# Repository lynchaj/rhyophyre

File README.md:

# rhyophyre
Single Board Computer featuring Zilog Z180 processor and NEC µPD7220 Graphics Display Controller

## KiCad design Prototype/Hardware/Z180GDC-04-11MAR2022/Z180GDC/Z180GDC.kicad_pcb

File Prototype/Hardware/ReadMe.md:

# rhyophyre prototype hardware folder

Contains KiCAD EDA files for schematic, PCB layout, 3D render, Bill of Materials, etc.

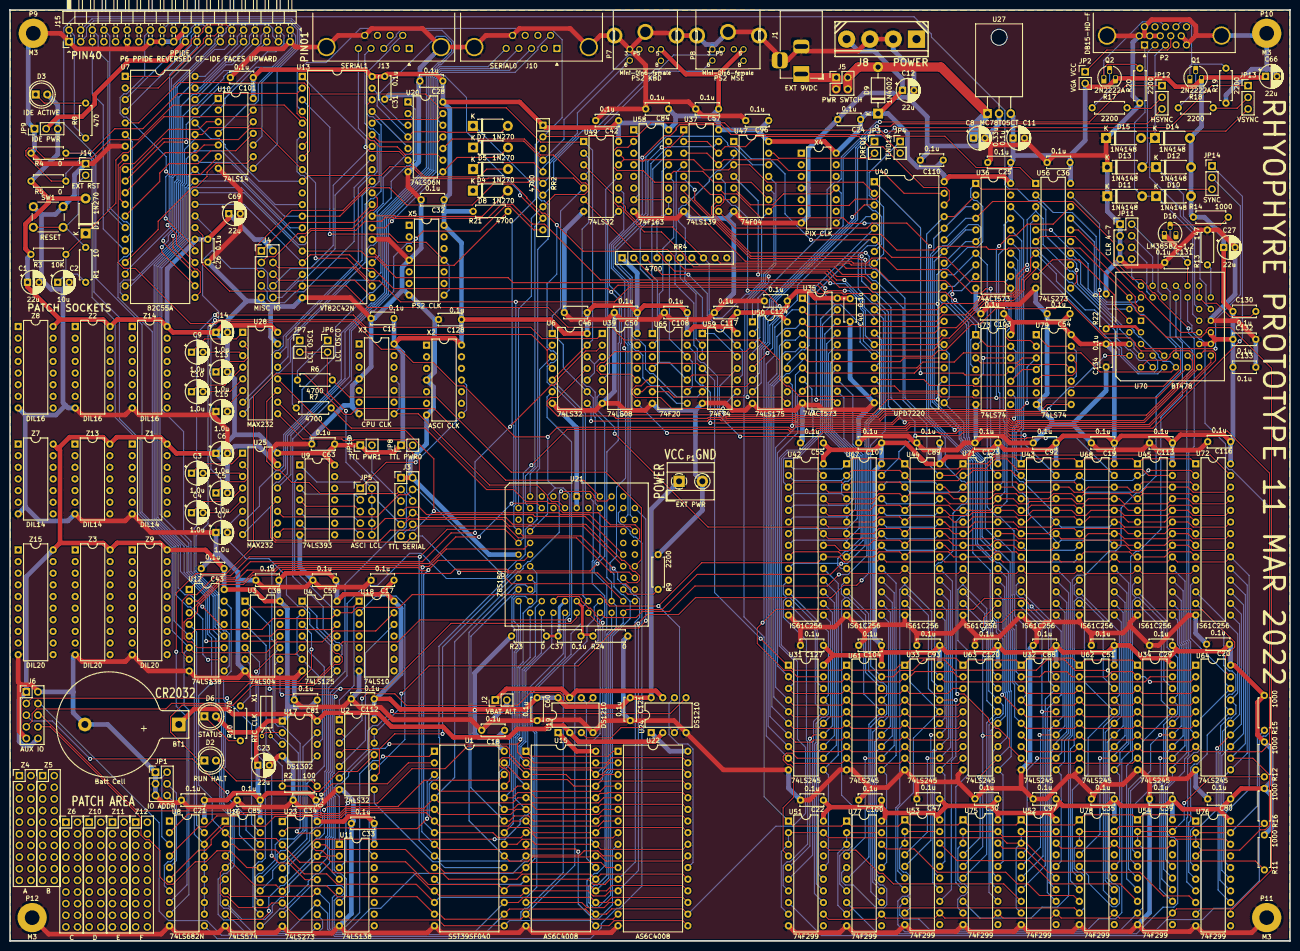
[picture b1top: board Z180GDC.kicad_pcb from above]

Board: 2 copper layers, 279.4 x 203.2 mm, 249 parts (0 on the bottom side), 388 nets.

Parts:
BT1: Batt Cell; BatteryHolder_Keystone_103_1x20mm
C1, C12, C23, C27, C66, C69: 22u; CP_Radial_D5.0mm_P2.50mm
C2: 10u; CP_Radial_D5.0mm_P2.50mm
C3, C4, C5, C6, C7, C9, C10, C13, C14, C15: 1.0u; CP_Radial_D5.0mm_P2.50mm
C8: 0.33u; CP_Radial_D5.0mm_P2.50mm
C11: 0.1u; CP_Radial_D5.0mm_P2.50mm
C16, C17, C18, C19, C20, C21, C22, C24, C25, C26, C28, C29, C30, C31, C32, C33, C34, C35, C36, C37, C38, C39, C40, C42, C43, C46, C47, C50, C51, C54, C55, C57, C59, C60, C63, C80, C81, C84, C85, C88, C89, C92, C93, C96, C97, C100, C101, C103, C104, C107, C108, C110, C112, C113, C116, C117, C120, C121, C123, C124, C127, C128, C130, C131, C132, C133, C134: 0.1u; C_Disc_D5.0mm_W2.5mm_P5.00mm
D1, D4, D5, D7, D8: 1N270; D_DO-41_SOD81_P7.62mm_Horizontal
D2: RUN HALT; LED_D5.0mm
D3: IDE ACTIVE; LED_D5.0mm
D6: STATUS; LED_D5.0mm
D9: 1N4002; D_DO-41_SOD81_P10.16mm_Horizontal
D10, D11, D12, D13, D14, D15: 1N4148; D_DO-41_SOD81_P7.62mm_Horizontal
D16: LM385BZ-1.2; TO-92L_HandSolder
J1: EXT 9VDC; BarrelJack_Horizontal
J2: VBAT ALT; PinHeader_1x02_P2.54mm_Vertical
J3: TTL SERIAL; PinHeader_2x06_P2.54mm_Vertical
J4: MISC IO; PinHeader_2x05_P2.54mm_Vertical
J5: PWR SWTCH; PinHeader_2x02_P2.54mm_Vertical
J6: AUX IO; PinHeader_2x05_P2.54mm_Vertical
J8: POWER; molex-drive-connector
J10: SERIAL0; DSUB-9_Male_Horizontal_P2.77x2.84mm_EdgePinOffset4.94mm_Hou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
J13: SERIAL1; DSUB-9_Male_Horizontal_P2.77x2.84mm_EdgePinOffset4.94mm_Hou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
J14: EXT RST; PinHeader_1x02_P2.54mm_Vertical
J15: PPIDE; PinHeader_2x20_P2.54mm_Horizontal
JP1: IO ADDR; PinHeader_2x03_P2.54mm_Vertical
JP2: VGA VCC; PinHeader_1x02_P2.54mm_Vertical
JP3: DREQ1; PinHeader_1x02_P2.54mm_Vertical
JP4: TEND1#; PinHeader_1x02_P2.54mm_Vertical
JP5: ASCI LCL; PinHeader_2x05_P2.54mm_Vertical
JP6: LCL OSC0; PinHeader_1x02_P2.54mm_Vertical
JP7: LCL OSC1; PinHeader_1x02_P2.54mm_Vertical
JP8: TTL PWR0; PinHeader_1x02_P2.54mm_Vertical
JP9: IDE PWR; PinHeader_1x03_P2.54mm_Vertical
JP10: TTL PWR1; PinHeader_1x02_P2.54mm_Vertical
JP11: CLR 4-7; PinHeader_2x04_P2.54mm_Vertical
JP12: HSYNC; PinHeader_1x03_P2.54mm_Vertical
JP13: VSYNC; PinHeader_1x03_P2.54mm_Vertical
JP14: SYNC; PinHeader_1x03_P2.54mm_Vertical
P1: EXT PWR; TerminalBlock_MetzConnect_Type101_RT01602HBWC_1x02_P5.08mm_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
P2: DB15-HD-F; DSUB-15-HD_Female_Horizontal_P2.29x1.98mm_EdgePinOffset3.03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
P7: PS2 KBD; mini-din6-female
P8: PS2 MSE; mini-din6-female
P9, P10, P11, P12: M3; MountingHole_3.2mm_M3_Pad
Q1, Q2: 2N2222A; TO-92L_HandSolder
R1: 10; R_Axial_DIN0207_L6.3mm_D2.5mm_P7.62mm_Horizontal
R2: 100; R_Axial_DIN0207_L6.3mm_D2.5mm_P7.62mm_Horizontal
R3: 10K; R_Axial_DIN0207_L6.3mm_D2.5mm_P7.62mm_Horizontal
R4, R5, R22, R23, R24: 0; R_Axial_DIN0207_L6.3mm_D2.5mm_P7.62mm_Horizontal
R6, R7, R21: 4700; R_Axial_DIN0207_L6.3mm_D2.5mm_P7.62mm_Horizontal
R8, R10: 470; R_Axial_DIN0207_L6.3mm_D2.5mm_P7.62mm_Horizontal
R9, R17, R18, R19, R20: 2200; R_Axial_DIN0207_L6.3mm_D2.5mm_P7.62mm_Horizontal
R11, R12, R14, R15, R16: 1000; R_Axial_DIN0207_L6.3mm_D2.5mm_P7.62mm_Horizontal
R13: 147; R_Axial_DIN0207_L6.3mm_D2.5mm_P7.62mm_Horizontal
RR2, RR4: 4700; R_Array_SIP10
SW1: RESET; SW_PUSH_6mm
U1: SST39SF040; DIP-32_W15.24mm
U2, U6, U49: 74LS32; DIP-14_W7.62mm
U3: 74LS04; DIP-14_W7.62mm
U4: 74LS125; DIP-14_W7.62mm
U7: 82C55A; DIP-40_W15.24mm
U8: 74LS682N; DIP-20_W7.62mm
U9: 74LS393; DIP-14_W7.62mm
U10: 74LS14; DIP-14_W7.62mm
U11, U12: 74LS138; DIP-16_W7.62mm
U13: VT82C42N; DIP-40_W15.24mm
U15, U22: AS6C4008; DIP-32_W15.24mm
U16: 74LS574; DIP-20_W7.62mm
U17: DS1302; DIP-8_W7.62mm
U18: 74LS10; DIP-14_W7.62mm
U19, U24: DS1210; DIP-8_W7.62mm
U20: 74LS06N; DIP-14_W7.62mm
U21: Z8S180; PLCC-68_THT-Socket
U23, U56: 74LS273; DIP-20_W7.62mm
U25, U28: MAX232; DIP-16_W7.62mm
U27: MC78T05CT; TO-220-3_Horizontal_TabDown
U31, U32, U33, U34, U61, U62, U63, U64: 74LS245; DIP-20_W7.62mm
U35, U36: 74ACT573; DIP-20_W7.62mm
U37: 74LS139; DIP-16_W7.62mm
U39: 74LS08; DIP-14_W7.62mm
U40: UPD7220; DIP-40_W15.24mm
U42, U43, U44, U45, U67, U68, U71, U72: IS61C256; DIP-28_W7.62mm
U47: 74F04; DIP-14_W7.62mm
U50: 74LS175; DIP-16_W7.62mm
U51, U52, U53, U54, U75, U76, U77, U78: 74F299; DIP-20_W7.62mm
U58: 74F163; DIP-16_W7.62mm
U59: 74F74; DIP-14_W7.62mm
U65: 74F20; DIP-14_W7.62mm
U70: BT478; PLCC-44_THT-Socket
U73, U79: 74LS74; DIP-14_W7.62mm
X1: RTC CLK; Crystal_C26-LF_D2.1mm_L6.5mm_Horizontal
X2: ASCI CLK; DIP-14_W7.62mm
X3: CPU CLK; DIP-14_W7.62mm
X4: PIX CLK; DIP-14_W7.62mm
X5: PS2 CLK; DIP-14_W7.62mm
Z1, Z7, Z13: DIL14; DIP-14_W7.62mm
Z2, Z8, Z14: DIL16; DIP-16_W7.62mm
Z3, Z9, Z15: DIL20; DIP-20_W7.62mm
Z4: A; PinHeader_2x10_P2.54mm_Vertical
Z5: B; PinHeader_2x10_P2.54mm_Vertical
Z6: C; PinHeader_2x10_P2.54mm_Vertical
Z10: D; PinHeader_2x10_P2.54mm_Vertical
Z11: E; PinHeader_2x10_P2.54mm_Vertical
Z12: F; PinHeader_2x10_P2.54mm_Vertical

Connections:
/2xWCLK: RR4.8, U40.1, U47.8, U49.9, U73.11, U79.11
/2xWCLK#: U47.9, U58.12, U59.11, U65.4, U65.10, U73.3, U79.3
/8-16: U56.19, U70.2
/9VDC: J1.1, J5.1, J5.3
/A0: U1.12, U7.9, U13.9, U15.12, U21.14, U22.12, U40.11, U70.17
/A1: U1.11, U7.8, U15.11, U21.15, U22.11, U70.18
/A2: U1.10, U12.1, U15.10, U21.16, U22.10, U70.19
/A3: U1.9, U12.2, U15.9, U21.17, U22.9
/A4: U1.8, U12.3, U15.8, U21.19, U22.8
/A5: U1.7, U8.6, U15.7, U21.20, U22.7
/A6: U1.6, U8.4, U15.6, U21.21, U22.6
/A7: U1.5, U8.2, U15.5, U21.22, U22.5
/A8: U1.27, U15.27, U21.23, U22.27
/A9: U1.26, U15.26, U21.24, U22.26
/A10: U1.23, U15.23, U21.25, U22.23
/A11: U1.25, U15.25, U21.26, U22.25
/A12: U1.4, U15.4, U21.27, U22.4
/A13: U1.28, U15.28, U21.28, U22.28
/A14: U1.29, U15.3, U21.29, U22.3
/A15: U11.1, U15.31, U21.30, U22.31
/A15_ROM: U1.3, U23.2
/A16: U11.2, U15.2, U21.31, U22.2
/A16_ROM: U1.2, U23.5
/A17: U11.3, U15.30, U21.32, U22.30
/A17_ROM: U1.30, U23.6
/A18: U11.5, U15.1, U21.33, U22.1
/A18_ROM: U1.1, U23.9
/A19: U3.1, U11.4, U21.35
/A19_ROM: J6.4, U23.12
/AD0: U31.2, U33.2, U35.9, U40.22, U61.2, U63.2
/AD1: U31.3, U33.3, U35.8, U40.23, U61.3, U63.3
/AD2: U31.4, U33.4, U35.7, U40.24, U61.4, U63.4
/AD3: U31.5, U33.5, U35.6, U40.25, U61.5, U63.5
/AD4: U31.6, U33.6, U35.5, U40.26, U61.6, U63.6
/AD5: U31.7, U33.7, U35.4, U40.27, U61.7, U63.7
/AD6: U31.8, U33.8, U35.3, U40.28, U61.8, U63.8
/AD7: U31.9, U33.9, U35.2, U40.29, U61.9, U63.9
/AD8: U32.2, U34.2, U36.9, U40.30, U62.2, U64.2
/AD9: U32.3, U34.3, U36.8, U40.31, U62.3, U64.3
/AD10: U32.4, U34.4, U36.7, U40.32, U62.4, U64.4
/AD11: U32.5, U34.5, U36.6, U40.33, U62.5, U64.5
/AD12: U32.6, U34.6, U36.5, U40.34, U62.6, U64.6
/AD13: U32.7, U34.7, U36.4, U40.35, U62.7, U64.7
/AD14: U32.8, U34.8, U36.3, U40.36, U62.8, U64.8
/AD15: U32.9, U34.9, U36.2, U40.37, U62.9, U64.9
/AD16: U37.2, U37.14, U40.38
/AD17: U37.3, U37.13, U40.39
/ALE: U35.11, U36.11, U40.6, U47.1, U79.2
/ALE2#: U49.10, U79.8
/ALE#: U47.2, U59.1, U59.12
/BLANK#: U50.11, U70.7
/BLU: D14.1, D15.2, P2.3, U70.27
/BUF_Q0: J6.3, U16.19
/BUF_Q1: J6.5, U16.18
/BUF_Q2: J6.6, U16.17
/BUF_Q3: J6.8, U16.16
/BUF_Q4: U16.15, U17.5
/BUF_Q5: U4.4, U16.14
/BUF_Q6: U16.13, U17.7
/BUF_Q7: U4.5, U16.12
/COLOR0: U51.8, U70.32
/COLOR1: U70.33, U77.8
/COLOR2: U53.8, U70.34
/COLOR3: U70.35, U75.8
/COLOR4: JP11.2, U70.36
/COLOR5: JP11.4, U70.37
/COLOR6: JP11.6, U70.38
/COLOR7: JP11.8, U70.39
/CS_ACR#: U12.15, U23.11
/CS_GDC#: U12.11, U49.2, U49.4
/CS_KM#: U12.12, U13.6
/CS_LATCH#: U12.10, U56.11
/CS_PPI#: U7.6, U12.13
/CS_RAMDAC0#: U12.9, U39.1
/CS_RAMDAC1#: U12.7, U39.2
/CS_RAMDAC#: U6.10, U6.12, U39.3
/CS_RAMHI#: U2.3, U19.5
/CS_RAMLO#: U2.6, U24.5
/CS_ROM#: U1.22, U2.8
/CS_RTC#: U6.2, U6.4, U12.14
/CTS0: J10.6, U25.13
/CTS1: J13.6, U28.13
/CTS_TTL0: J3.12, U21.46, U25.12
/CTS_TTL1: J3.11, U21.56, U28.12
/D0: U1.13, U4.3, U7.34, U13.12, U15.13, U16.2, U21.37, U22.13, U23.3, U40.12, U56.3, U70.8
/D1: U1.14, U7.33, U13.13, U15.14, U16.3, U21.38, U22.14, U23.4, U40.13, U56.4, U70.9
/D2: U1.15, U7.32, U13.14, U15.15, U16.4, U21.39, U22.15, U23.7, U40.14, U56.7, U70.10
/D3: U1.17, U7.31, U13.15, U15.17, U16.5, U21.40, U22.17, U23.8, U40.15, U56.8, U70.11
/D4: U1.18, U7.30, U13.16, U15.18, U16.6, U21.41, U22.18, U23.13, U40.16, U56.13, U70.12
/D5: U1.19, U7.29, U13.17, U15.19, U16.7, U21.42, U22.19, U23.14, U40.17, U56.14, U70.13
/D6: U1.20, U4.8, U7.28, U13.18, U15.20, U16.8, U21.43, U22.20, U23.17, U40.18, U56.17, U70.14
/D7: U1.21, U7.27, U13.19, U15.21, U16.9, U21.44, U22.21, U23.18, U40.19, U56.18, U70.15
/DBIN: U47.4, U73.2
/DBIN#: U31.1, U32.1, U33.1, U34.1, U39.4, U49.11, U59.4, U61.1, U62.1, U63.1, U64.1
/DEBL0#: U31.19, U32.19, U37.12
/DEBL1#: U37.11, U61.19, U62.19
/DEBL2#: U33.19, U34.19, U37.10
/DEBL3#: U37.9, U63.19, U64.19
/DEBL#: U37.15, U59.6
/DREQ0#: R6.2, U21.50
/DREQ1#: U21.58, U47.12
/GND_BT478: R22.1, U70.3
/GND_CPU: C37.2, R24.1, U21.36
/GRE: D12.1, D13.2, P2.2, U70.26
/H-Sync: P2.13, Q2.1, R20.2
/HALT#: U2.12, U2.13, U21.60
/HSYNC#: JP12.2, R17.2
/HSYNC+: JP12.1, U50.2
/HSYNC-: JP12.3, U39.10, U50.3
/IDE-LED: D3.1, R8.2
/INP_D6: J6.7, RR2.10, U4.9
/INT0#: RR2.8, U20.10, U21.10
/INT1#: RR2.9, U20.12, U21.11
/IORD#: U40.9, U49.3
/IORQ#: U8.11, U21.62
/IOSEL#: U8.19, U12.4
/IOWR#: U40.10, U49.6
/KBDCLK: D4.2, U13.1, U20.6
/KBDDAT: D5.2, U13.27, U20.8
/KEYCLOCK: D4.1, P7.6, RR2.5
/KEYDATA: D5.1, P7.1, RR2.4
/M1#: U8.8, U21.65
/MA0: U35.12, U42.10, U43.10, U44.10, U45.10, U67.10, U68.10, U71.10, U72.10
/MA1: U35.13, U42.9, U43.9, U44.9, U45.9, U67.9, U68.9, U71.9, U72.9
/MA2: U35.14, U42.8, U43.8, U44.8, U45.8, U67.8, U68.8, U71.8, U72.8
/MA3: U35.15, U42.7, U43.7, U44.7, U45.7, U67.7, U68.7, U71.7, U72.7
/MA4: U35.16, U42.6, U43.6, U44.6, U45.6, U67.6, U68.6, U71.6, U72.6
/MA5: U35.17, U42.5, U43.5, U44.5, U45.5, U67.5, U68.5, U71.5, U72.5
/MA6: U35.18, U42.4, U43.4, U44.4, U45.4, U67.4, U68.4, U71.4, U72.4
/MA7: U35.19, U42.3, U43.3, U44.3, U45.3, U67.3, U68.3, U71.3, U72.3
/MA8: U36.12, U42.25, U43.25, U44.25, U45.25, U67.25, U68.25, U71.25, U72.25
/MA9: U36.13, U42.24, U43.24, U44.24, U45.24, U67.24, U68.24, U71.24, U72.24
/MA10: U36.14, U42.21, U43.21, U44.21, U45.21, U67.21, U68.21, U71.21, U72.21
/MA11: U36.15, U42.23, U43.23, U44.23, U45.23, U67.23, U68.23, U71.23, U72.23
/MA12: U36.16, U42.2, U43.2, U44.2, U45.2, U67.2, U68.2, U71.2, U72.2
/MA13: U36.17, U42.26, U43.26, U44.26, U45.26, U67.26, U68.26, U71.26, U72.26
/MA14: U36.18, U42.1, U43.1, U44.1, U45.1, U67.1, U68.1, U71.1, U72.1
/MOUSECLOCK: D7.1, P8.6, RR2.7
/MOUSEDATA: D8.1, P8.1, RR2.6
/MREQ#: U2.2, U2.4, U2.9, U21.63
/MSECLK: D7.2, U13.39, U20.4
/MSEDAT: D8.2, U13.28, U20.2
/NMI#: RR2.3, U21.9
/OL0: U56.2, U70.41
/OL1: U56.5, U70.42
/OL2: U56.6, U70.43
/OL3: U56.9, U70.44
/ONE: R5.2, U8.9, U12.6, U13.5, U18.13
/P12: J4.1, U13.29
/P13: J4.3, U13.30
/P14: J4.5, U13.31
/P15: J4.7, U13.32
/P16: J4.10, U13.33
/P17: J4.8, U13.34
/P20: J4.6, U13.21
/P21: J4.4, U13.22
/P24-OB: U13.35, U20.11
/P25-BF: U13.36, U20.13
/PA0: J15.24, U7.4
/PA1: J15.26, U7.3
/PA2: J15.28, U7.2
/PA3: J15.30, U7.1
/PA4: J15.32, U7.40
/PA5: J15.34, U7.39
/PA6: J15.36, U7.38
/PA7: J15.38, U7.37
/PB0: J15.37, U7.18
/PB1: J15.35, U7.19
/PB2: J15.33, U7.20
/PB3: J15.31, U7.21
/PB4: J15.29, U7.22
/PB5: J15.27, U7.23
/PB6: J15.25, U7.24
/PB7: J15.23, U7.25
/PC0: J15.6, U7.14
/PC1: J15.8, U7.15
/PC2: J15.5, U7.16
/PC3: U7.17, U10.9
/PC3#: J15.4, U10.8
/PC4: U7.13, U10.11
/PC4#: J15.3, U10.10
/PC5: U7.12, U10.3
/PC5#: J15.18, U10.4
/PC6: U7.11, U10.5
/PC6#: J15.16, U10.6
/PC7: U7.10, U10.1
/PC7#: J15.40, U10.2
/PIX-CLK: U47.6, U51.12, U52.12, U53.12, U54.12, U58.2, U70.40, U75.12, U76.12, U77.12, U78.12
/PIX-CLK#: U47.5, X4.8, X4.11
/PPWR: J15.21, JP9.2
/PROG: R21.2, U13.25
/PU4.7K-H: RR4.2, U50.1
/PU4.7K-I: RR4.3, U59.10, U59.13
/PU4.7K-J: RR4.4, U58.1, U58.7, U58.9, U58.10
/PU4.7K-K: RR4.5, U65.9, U65.12
/PU4.7K-L: RR4.6, U59.2, U59.3
/PU4.7K-M: RR4.7, U73.1, U73.4, U73.10, U73.13, U79.1, U79.4, U79.10, U79.13
/PU4.7K-O: JP4.1, RR4.9, U40.8
/RD#: U1.24, U6.5, U6.13, U7.5, U13.8, U15.24, U21.67, U22.24, U49.1
/RD-GDC#: U39.5, U49.8
/RD_RAMDAC#: U6.11, U70.6
/READ-VRAM#: U39.6, U42.22, U43.22, U44.22, U45.22, U67.22, U68.22, U71.22, U72.22
/RED: D10.1, D11.2, P2.1, U70.25
/RESET: U3.11, U7.35, U10.12
/RESET#: RR2.2, U3.10, U13.4, U21.8, U23.1, U56.1
/ROM_DEC#: U2.10, U11.15, U18.2
/ROM_ENABLE: U3.8, U11.6
/ROM_ENABLE#: U3.9, U23.19
/RTC_DQ: U4.2, U4.6, U17.6
/RTC_RD#: U4.1, U4.10, U6.6
/RTC_WR#: U6.3, U16.11
/RTS0: J10.4, U25.14
/RTS1: J13.4, U28.14
/RTS_TTL0: J3.4, U21.45, U25.11
/RTS_TTL1: J3.3, U23.16, U28.11
/RUN-HALT-A: D2.1, U4.11
/RUN-HALT-B: D2.2, R2.1
/RX0: J10.3, U25.8
/RX1: J13.3, U28.8
/SETUP: U56.16, U70.23
/SIN_TTL0: J3.8, U21.49, U25.9
/SIN_TTL1: J3.7, U21.53, U28.9
/SOUT_TTL0: J3.10, U21.48, U25.10
/SOUT_TTL1: J3.9, U21.51, U28.10
/STATUS#: U3.5, U23.15
/STATUS-LED: D6.1, R10.2
/TEND0#: R7.2, U21.54
/TEND1#: JP4.2, U21.59
/TX0: J10.5, U25.7
/TX1: J13.5, U28.7
/V0D0: U31.18, U42.11, U51.7
/V0D1: U31.17, U42.12, U51.13
/V0D2: U31.16, U42.13, U51.6
/V0D3: U31.15, U42.15, U51.14
/V0D4: U31.14, U42.16, U51.5
/V0D5: U31.13, U42.17, U51.15
/V0D6: U31.12, U42.18, U51.4
/V0D7: U31.11, U42.19, U51.16
/V0D8: U32.18, U43.11, U52.7
/V0D9: U32.17, U43.12, U52.13
/V0D10: U32.16, U43.13, U52.6
/V0D11: U32.15, U43.15, U52.14
/V0D12: U32.14, U43.16, U52.5
/V0D13: U32.13, U43.17, U52.15
/V0D14: U32.12, U43.18, U52.4
/V0D15: U32.11, U43.19, U52.16
/V1D0: U61.18, U67.11, U77.7
/V1D1: U61.17, U67.12, U77.13
/V1D2: U61.16, U67.13, U77.6
/V1D3: U61.15, U67.15, U77.14
/V1D4: U61.14, U67.16, U77.5
/V1D5: U61.13, U67.17, U77.15
/V1D6: U61.12, U67.18, U77.4
/V1D7: U61.11, U67.19, U77.16
/V1D8: U62.18, U68.11, U78.7
/V1D9: U62.17, U68.12, U78.13
/V1D10: U62.16, U68.13, U78.6
/V1D11: U62.15, U68.15, U78.14
/V1D12: U62.14, U68.16, U78.5
/V1D13: U62.13, U68.17, U78.15
/V1D14: U62.12, U68.18, U78.4
/V1D15: U62.11, U68.19, U78.16
/V2D0: U33.18, U44.11, U53.7
/V2D1: U33.17, U44.12, U53.13
/V2D2: U33.16, U44.13, U53.6
/V2D3: U33.15, U44.15, U53.14
/V2D4: U33.14, U44.16, U53.5
/V2D5: U33.13, U44.17, U53.15
/V2D6: U33.12, U44.18, U53.4
/V2D7: U33.11, U44.19, U53.16
/V2D8: U34.18, U45.11, U54.7
/V2D9: U34.17, U45.12, U54.13
/V2D10: U34.16, U45.13, U54.6
/V2D11: U34.15, U45.15, U54.14
/V2D12: U34.14, U45.16, U54.5
/V2D13: U34.13, U45.17, U54.15
/V2D14: U34.12, U45.18, U54.4
/V2D15: U34.11, U45.19, U54.16
/V3D0: U63.18, U71.11, U75.7
/V3D1: U63.17, U71.12, U75.13
/V3D2: U63.16, U71.13, U75.6
/V3D3: U63.15, U71.15, U75.14
/V3D4: U63.14, U71.16, U75.5
/V3D5: U63.13, U71.17, U75.15
/V3D6: U63.12, U71.18, U75.4
/V3D7: U63.11, U71.19, U75.16
/V3D8: U64.18, U72.11, U76.7
/V3D9: U64.17, U72.12, U76.13
/V3D10: U64.16, U72.13, U76.6
/V3D11: U64.15, U72.15, U76.14
/V3D12: U64.14, U72.16, U76.5
/V3D13: U64.13, U72.17, U76.15
/V3D14: U64.12, U72.18, U76.4
/V3D15: U64.11, U72.19, U76.16
/V-Sync: P2.14, Q1.1, R19.2
/VBAT_ALT: J2.1, U19.7, U24.7
/VBAT_SRAM: BT1.1, U17.8, U19.2, U24.2
/VCC_CPU: C37.1, R23.1, U21.34
/VCC_SRAM0: U22.32, U24.1
/VCC_SRAM1: U15.32, U19.1
/VCC_VGA: JP2.1, P2.9
/VIN: C8.1, D9.2, J5.2, J5.4, U27.VI
/VSR-LD: U47.10, U51.1, U52.1, U53.1, U54.1, U75.1, U76.1, U77.1, U78.1
/VSR-LD#: U47.11, U50.9, U65.6
/VSYNC#: JP13.2, R18.2
/VSYNC+: JP13.1, U50.7
/VSYNC-: JP13.3, U39.9, U50.6
/WE0#: U37.4, U42.27, U43.27
/WE1#: U37.5, U67.27, U68.27
/WE2#: U37.6, U44.27, U45.27
/WE3#: U37.7, U71.27, U72.27
/WE#: U37.1, U65.8
/WR#: U1.31, U6.1, U6.9, U7.36, U13.10, U15.29, U21.66, U22.29, U49.5
/WR_RAMDAC#: U6.8, U70.16
/ZERO: JP14.3, R4.2, U4.13, U8.12, U8.13, U8.14, U8.15, U8.16, U8.17, U8.18, U9.2, U12.5, U13.2, U13.7, U16.1, U19.3, U24.3, U35.1, U36.1, U40.21, U42.20, U43.20, U44.20, U45.20, U52.18, U54.18, U67.20, U68.20, U71.20, U72.20, U76.18, U78.18
GND: BT1.2, C1.2, C2.2, C6.2, C7.1, C8.2, C11.2, C12.2, C14.2, C15.1, C16.2, C17.2, C18.2, C19.2, C20.2, C21.2, C22.2, C23.2, C24.2, C25.2, C26.2, C27.2, C28.2, C29.2, C30.2, C31.2, C32.2, C33.2, C34.2, C35.2, C36.2, C38.2, C39.2, C40.2, C42.2, C43.2, C46.2, C47.2, C50.2, C51.2, C54.2, C55.2, C57.2, C59.2, C60.2, C63.2, C66.2, C69.2, C80.2, C81.2, C84.2, C85.2, C88.2, C89.2, C92.2, C93.2, C96.2, C97.2, C100.2, C101.2, C103.2, C104.2, C107.2, C108.2, C110.2, C112.2, C113.2, C116.2, C117.2, C120.2, C121.2, C123.2, C124.2, C127.2, C128.2, C131.2, C132.2, C133.2, C134.2, D11.1, D13.1, D15.1, D16.1, J1.2, J1.3, J2.2, J3.1, J3.2, J4.9, J6.2, J6.9, J8.2, J8.3, J10.0, J10.9, J13.0, J13.9, J14.1, J15.1, J15.11, J15.15, J15.17, J15.19, J15.22, J15.39, JP1.1, JP1.3, JP1.5, JP9.1, JP11.1, JP11.3, JP11.5, JP11.7, P1.2, P2.0, P2.5, P2.6, P2.7, P2.8, P2.10, P2.11, P7.3, P7.SH1, P7.SH2, P7.SH3, P8.3, P8.SH1, P8.SH2, P8.SH3, P9.1, P10.1, P11.1, P12.1, R4.1, R9.1, R13.2, R19.1, R20.1, R22.2, R24.2, SW1.1, U1.16, U2.7, U3.7, U4.7, U6.7, U7.7, U8.10, U9.7, U10.7, U11.8, U12.8, U13.20, U13.26, U15.16, U16.10, U17.4, U18.7, U19.4, U20.7, U21.1, U21.2, U21.18, U22.16, U23.10, U24.4, U25.15, U27.GND, U28.15, U31.10, U32.10, U33.10, U34.10, U35.10, U36.10, U37.8, U39.7, U40.20, U42.14, U43.14, U44.14, U45.14, U47.7, U49.7, U50.8, U51.10, U52.10, U53.10, U54.10, U56.10, U58.8, U59.7, U61.10, U62.10, U63.10, U64.10, U65.7, U67.14, U68.14, U70.24, U71.14, U72.14, U73.7, U75.10, U76.10, U77.10, U78.10, U79.7, X2.4, X2.7, X3.4, X3.7, X4.4, X4.7, X5.4, X5.7, Z1.7, Z2.8, Z3.10, Z7.7, Z8.8, Z9.10, Z13.7, Z14.8, Z15.10
unnamed: C2.1, D1.1, R1.1, R3.2, U10.13
unnamed: C3.1, U25.1
unnamed: C3.2, U25.3
unnamed: C4.1, U25.4
unnamed: C4.2, U25.5
unnamed: C5.1, U25.2
unnamed: C7.2, U25.6
unnamed: C9.1, U28.1
unnamed: C9.2, U28.3
unnamed: C10.1, U28.4
unnamed: C10.2, U28.5
unnamed: C13.1, U28.2
unnamed: C15.2, U28.6
unnamed: C130.2, U70.29, U70.30
unnamed: C131.1, D16.2, R14.2, U70.31
unnamed: J3.5, JP10.2
unnamed: J3.6, JP8.2
unnamed: J14.2, R1.2, SW1.2
unnamed: J15.2, R8.1
unnamed: JP1.2, U8.3
unnamed: JP1.4, U8.5
unnamed: JP1.6, U8.7
unnamed: JP3.1, U40.7
unnamed: JP3.2, U47.13
unnamed: JP5.1, U9.1, X2.8, X2.11
unnamed: JP5.3, U9.3
unnamed: JP5.5, U9.4
unnamed: JP5.7, U9.5
unnamed: JP5.9, U9.6
unnamed: JP5.2, JP5.4, JP5.6, JP5.8, JP5.10, JP6.2, JP7.2
unnamed: JP6.1, R6.1
unnamed: JP7.1, R7.1
unnamed: JP14.1, U39.8
unnamed: JP14.2, U70.5
unnamed: Q1.2, R18.1
unnamed: Q2.2, R17.1
unnamed: R2.2, U2.11, U3.3
unnamed: R9.2, U21.47
unnamed: R10.1, U3.6
unnamed: R11.2, U51.2, U51.3, U51.9, U51.19, U52.2, U52.3, U52.9, U52.19
unnamed: R12.2, U53.2, U53.3, U53.9, U53.19, U54.2, U54.3, U54.9, U54.19
unnamed: R13.1, U70.28
unnamed: R15.2, U75.2, U75.3, U75.9, U75.19, U76.2, U76.3, U76.9, U76.19
unnamed: R16.2, U77.2, U77.3, U77.9, U77.19, U78.2, U78.3, U78.9, U78.19
unnamed: U3.4, U4.12
unnamed: U13.3, X5.8, X5.11
unnamed: U13.23, U20.1
unnamed: U13.24, U20.3
unnamed: U13.37, U20.5
unnamed: U13.38, U20.9
unnamed: U15.22, U19.6
unnamed: U17.2, X1.2
unnamed: U17.3, X1.1
unnamed: U2.1, U3.2, U18.1
unnamed: U2.5, U18.12
unnamed: U21.4, X3.8, X3.11
unnamed: U22.22, U24.6
unnamed: U40.2, U47.3, U49.12, U49.13
unnamed: U40.3, U50.4
unnamed: U40.4, U50.5
unnamed: U40.5, U50.12
unnamed: U51.18, U52.8
unnamed: U53.18, U54.8
unnamed: U58.13, U65.2
unnamed: U58.14, U65.1
unnamed: U59.9, U65.5
unnamed: U65.13, U73.9
unnamed: U73.5, U73.12
unnamed: U75.18, U76.8
unnamed: U77.18, U78.8
unnamed: U79.5, U79.12
VCC: C1.1, C5.2, C6.1, C11.1, C12.1, C13.2, C14.1, C16.1, C17.1, C18.1, C19.1, C20.1, C21.1, C22.1, C23.1, C24.1, C25.1, C26.1, C27.1, C28.1, C29.1, C30.1, C31.1, C32.1, C33.1, C34.1, C35.1, C36.1, C38.1, C39.1, C40.1, C42.1, C43.1, C46.1, C47.1, C50.1, C51.1, C54.1, C55.1, C57.1, C59.1, C60.1, C63.1, C66.1, C69.1, C80.1, C81.1, C84.1, C85.1, C88.1, C89.1, C92.1, C93.1, C96.1, C97.1, C100.1, C101.1, C103.1, C104.1, C107.1, C108.1, C110.1, C112.1, C113.1, C116.1, C117.1, C120.1, C121.1, C123.1, C124.1, C127.1, C128.1, C130.1, C132.1, C133.1, C134.1, D1.2, D3.2, D6.2, D9.1, D10.2, D12.2, D14.2, J4.2, J6.1, J6.10, J8.4, JP2.2, JP8.1, JP9.3, JP10.1, P1.1, P7.5, P8.5, Q1.3, Q2.3, R3.1, R5.1, R11.1, R12.1, R14.1, R15.1, R16.1, R21.1, R23.2, RR2.1, RR4.1, U1.32, U2.14, U3.14, U4.14, U6.14, U7.26, U8.20, U9.14, U10.14, U11.16, U12.16, U13.40, U16.20, U17.1, U18.14, U19.8, U20.14, U23.20, U24.8, U25.16, U27.VO, U28.16, U31.20, U32.20, U33.20, U34.20, U35.20, U36.20, U37.16, U39.14, U40.40, U42.28, U43.28, U44.28, U45.28, U47.14, U49.14, U50.16, U51.20, U52.20, U53.20, U54.20, U56.20, U58.16, U59.14, U61.20, U62.20, U63.20, U64.20, U65.14, U67.28, U68.28, U70.4, U70.20, U70.21, U70.22, U71.28, U72.28, U73.14, U75.20, U76.20, U77.20, U78.20, U79.14, X2.14, X3.14, X4.14, X5.14, Z1.14, Z2.16, Z3.20, Z7.14, Z8.16, Z9.20, Z13.14, Z14.16, Z15.20

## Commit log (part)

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2022-03-30 Remove some SBC188 related stuff.
2022-03-30 Remove more unneeded files.
2022-03-30 Port to RHYOPHYRE
2022-03-30 Add executable for now.
2022-03-30 Rename files to lowercase.
2022-03-30 Remove SBC188 related stuff.
2022-03-30 Port to rhyophyre.
2022-03-30 Add executables for now.
2022-04-01 Set sync params to match t7220.asm
2022-04-01 testgdc program work
2022-04-01 Print output values for debug.
    Sync more with Dan's settings.
2022-04-02 GDC test
2022-04-03 D7220.COM now works when compiled with SDCC.
2022-04-03 source clean up
2022-04-03 Start process of creating application library.
    This commit creates a new software directory and
    splits the D7220 test program into a d7220.c main
    program and a gdc7220.c library containing the GDC
    routines.
    Also, added a program to draw a Koch snowflake.
2022-04-04 Add ability to build the code with CMake.
2022-04-05 Add fast clear screen; general cleanup
2022-04-09 Add a program to display PCX bitmap images.
    - Added a few sample images.
    - Added option to D7220 to display checkboard pattern.
2022-04-26 Add Scrolling Functionality
2022-04-26 Fix various SDCC compile errors/warnings.
2022-04-28 Add TEXT Application
    The TEXT application demonstrates text processing on the 7220. It initially displays all characters of the font. It then provides a dumb terminal mechanism with scrolling.
2022-04-29 TEXT Application Cleanup
    - Move font data to separate file
    - Parameter driven execution
    - Can now "type" a file to display
    - Optional inter-character delay
    - Add key to perform reverse linefeed
    - Add key to perform color change
2022-04-29 Create font7220.h
    Forgot font data file.
2022-04-29 Add Timer to TEXT Application
    TEXT application will now measure (in ticks) time taken to send a file to the display.
2022-05-01 Work in progress for DMA support.
2022-05-01 Add dma.h file
2022-05-03 Fixes that make DMA work.
2022-05-03 Fix Makefile; clean up code.
2022-09-25 Add files via upload
    Sample configuration file for Andrew Lynch system
